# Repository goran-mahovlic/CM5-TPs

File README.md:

# CM5 Test Point Breakout

Sveden projekt za KiCad izveden iz obratno projektirane ploče Raspberry Pi Compute Module 5 ([schlae/cm5-reveng](https://github.com/schlae/cm5-reveng), CC BY-SA 4.0, autor Tube Time).

Sadrži **samo** ono što treba za pristup mjernim točkama modula:

| Element                        | Količina | Sloj         | Napomena                                                       |
|--------------------------------|----------|--------------|----------------------------------------------------------------|
| Test-točke `TP*`               | 58       | B.Cu (donji) | pad promjera 1,0 mm                                            |
| Konektori modula `J3`, `J4`    | 2        | B.Cu (donji) | Amphenol 10164228-1001A1RLF, 2 × 100 nožica + 4 mehanička pada |
| Rupe za pričvršćenje `H1`–`H4` | 4        | kroz ploču   | raspored 48,0 × 33,0 mm                                        |
| Obris ploče `Edge.Cuts`        | 8 crta   | –            | 55,00 × 40,00 mm, zaobljeni kutovi                             |

Vodovi, zone, ostale sastavnice i unutarnji slojevi izostavljeni su. Geometrija je preuzeta **1:1**, pa se položaji poklapaju s pravim modulom.

*Donji sloj: 58 test-točaka, konektori J3 (gore) i J4 (dolje), četiri rupe u uglovima. Natpisi J3/J4 zrcaljeni su jer su na donjem sloju.*

## Datoteke

```
cm5_tp_breakout.kicad_pro      projekt
cm5_tp_breakout.kicad_sch      korijenska shema (tri lista)
  testpoints.kicad_sch         58 test-točaka, opis uz svaku
  cm5_connectors.kicad_sch     J3 i J4 sa svim imenima mreža
  mechanical.kicad_sch         H1-H4
cm5_tp_breakout.kicad_pcb      ploča (dva sloja)
cm5_tp_breakout.kicad_sym      simboli (TestPoint, CM5_Conn_100P, MountingHole)
cm5_tp_breakout.pretty/        footprinti (izvezeni iz izvorne ploče)
doc/                           izvezena shema u PDF-u
tools/                         generator — projekt se može ponovno izgraditi iz izvornika
```

Projekt je samostalan: simboli i footprinti nalaze se u projektnim knjižnicama, pa ne treba nijedna vanjska knjižnica.

## Test-točke

Koordinate su u milimetrima od **donjega lijevog kuta ploče**, u KiCadovu pogledu odozgo (X udesno, Y prema gore). Točke su na donjem sloju, pa su pri pogledu odozdo zrcaljene po osi X.

`Oznaka` je natpis s izvorne ploče, `Mreža` je ime mreže u shemi, `Na konektoru` navodi nožice J3/J4 koje su na istoj mreži.

### Napajanje

| TP     | Oznaka       | Mreža            | Nazivno | X \[mm\] | Y \[mm\] | Na konektoru                             | Opis                                                                                                               |
|--------|--------------|------------------|---------|---------:|---------:|------------------------------------------|--------------------------------------------------------------------------------------------------------------------|
| `TP63` | 5V_SENSE     | `+5V`            | 5,0 V   |     8,70 |    18,20 | –                                        | 5 V iza sklopke s ograničenjem struje u PMIC-u DA9091; na ploči označeno 5V_SENSE — mjerna točka, ne opterećivati. |
| `TP1`  | 5V           | `+5VIN`          | 5,0 V   |    14,34 |    17,54 | J3-77, J3-79, J3-81, J3-83, J3-85, J3-87 | Ulazno napajanje modula s nosive ploče, prije sklopke PMIC-a (J3, nožice 77–87).                                   |
| `TP78` | 5V           | `+5VIN`          | 5,0 V   |    14,37 |    19,52 | J3-77, J3-79, J3-81, J3-83, J3-85, J3-87 | Ulazno napajanje modula s nosive ploče, prije sklopke PMIC-a (J3, nožice 77–87).                                   |
| `TP34` | CM5_1V8      | `CM5_1V8`        | 1,8 V   |    50,50 |    15,50 | J3-88, J3-90                             | Sabirnica 1,8 V modula izvedena na konektor (J3, nožice 88 i 90).                                                  |
| `TP33` | CM5_3V3      | `CM5_3V3`        | 3,3 V   |    47,00 |    36,00 | J3-84, J3-86                             | Sabirnica 3,3 V modula izvedena na konektor (J3, nožice 84 i 86).                                                  |
| `TP64` | VDD_1V0_PHY  | `ETHPHY_U4_VREG` | –       |    47,30 |     5,40 | –                                        | Izlaz unutarnjega regulatora ethernetskoga PHY-ja BCM54210PE (U4), nožica VREG; na ploči označeno VDD_1V0_PHY.     |
| `TP77` | GPIO_VREF    | `GPIO_VREF`      | 3,3 V   |    45,00 |    37,00 | J3-78                                    | Referentni napon skupine GPIO na RP1; određuje logičke razine (J3, nožica 78).                                     |
| `TP30` | 0V6          | `VDD_0V6`        | 0,6 V   |    37,20 |    34,90 | –                                        | VDDQ za LPDDR4X (U2) iz PMIC-a; osjetljivo na šum i pad napona.                                                    |
| `TP29` | VDD_0V8_BCM  | `VDD_0V8_BCM`    | 0,8 V   |    23,65 |    21,55 | –                                        | Pomoćna sabirnica 0,8 V za BCM2712.                                                                                |
| `TP15` | VDD_0V8_LDO  | `VDD_0V8_LDO`    | 0,8 V   |    14,70 |     6,60 | –                                        | Izlaz linearnoga regulatora 0,8 V (niskošumni dio).                                                                |
| `TP31` | 1V1          | `VDD_1V1`        | 1,1 V   |     9,10 |     3,20 | –                                        | Sabirnica 1,1 V (VDD1 memorije LPDDR4X i logika).                                                                  |
| `TP27` | VDD_1V1_RP1  | `VDD_1V1_RP1`    | 1,1 V   |    43,60 |    22,30 | –                                        | Jezgreno napajanje 1,1 V za ulazno-izlazni most RP1.                                                               |
| `TP45` | VDD_1V1_RP1  | `VDD_1V1_RP1`    | 1,1 V   |    53,10 |    28,70 | –                                        | Jezgreno napajanje 1,1 V za ulazno-izlazni most RP1.                                                               |
| `TP18` | VDD_1V8_2    | `VDD_1V8_2`      | 1,8 V   |    23,40 |    23,55 | –                                        | Druga grana 1,8 V (ulazi/izlazi i memorija).                                                                       |
| `TP44` | VDD_2V5_RP1  | `VDD_2V5_RP1`    | 2,5 V   |    51,70 |    30,20 | –                                        | Napajanje 2,5 V analognoga dijela RP1 (PLL i PHY).                                                                 |
| `TP17` | VDD_3V3_2    | `VDD_3V3_2`      | 3,3 V   |    37,40 |     8,10 | –                                        | Druga grana 3,3 V (ulazi/izlazi).                                                                                  |
| `TP32` | VDD_3V7_WIFI | `VDD_3V7_WIFI`   | 3,7 V   |     1,50 |    13,00 | –                                        | Napajanje modula WiFi/Bluetooth RP1-RM0 (U7).                                                                      |
| `TP28` | VDD_BCM_CORE | `VDD_BCM_CORE`   | ~0,8 V  |    15,40 |    16,00 | –                                        | Jezgreno napajanje SoC-a BCM2712; napon se mijenja s opterećenjem (DVFS).                                          |
| `TP9`  | VREF_3V3     | `VREF_3V3`       | 3,3 V   |     1,50 |    10,50 | –                                        | Referentnih 3,3 V (djelitelj napona, ne opterećivati).                                                             |
| `TP10` | VREG         | `VREG`           | –       |    48,40 |    15,10 | –                                        | Izlaz unutarnjega regulatora PMIC-a DA9091; mjerna točka, ne napajanje.                                            |

### Masa

| TP     | Oznaka | Mreža | Nazivno | X \[mm\] | Y \[mm\] | Na konektoru                         | Opis                                                           |
|--------|--------|-------|---------|---------:|---------:|--------------------------------------|----------------------------------------------------------------|
| `TP3`  | GND    | `GND` | 0 V     |    51,20 |    32,60 | J3-1, J3-2, J3-7, J3-8, J3-13, J3-14 | Masa. Referentna točka za sva mjerenja; devet točaka po ploči. |
| `TP7`  | GND    | `GND` | 0 V     |    24,20 |     7,50 | J3-1, J3-2, J3-7, J3-8, J3-13, J3-14 | Masa. Referentna točka za sva mjerenja; devet točaka po ploči. |
| `TP8`  | GND    | `GND` | 0 V     |     1,65 |    15,05 | J3-1, J3-2, J3-7, J3-8, J3-13, J3-14 | Masa. Referentna točka za sva mjerenja; devet točaka po ploči. |
| `TP13` | GND    | `GND` | 0 V     |    42,60 |     7,30 | J3-1, J3-2, J3-7, J3-8, J3-13, J3-14 | Masa. Referentna točka za sva mjerenja; devet točaka po ploči. |
| `TP26` | GND    | `GND` | 0 V     |    17,70 |    20,20 | J3-1, J3-2, J3-7, J3-8, J3-13, J3-14 | Masa. Referentna točka za sva mjerenja; devet točaka po ploči. |
| `TP46` | GND    | `GND` | 0 V     |     7,00 |    34,70 | J3-1, J3-2, J3-7, J3-8, J3-13, J3-14 | Masa. Referentna točka za sva mjerenja; devet točaka po ploči. |
| `TP60` | GND    | `GND` | 0 V     |    48,00 |    38,70 | J3-1, J3-2, J3-7, J3-8, J3-13, J3-14 | Masa. Referentna točka za sva mjerenja; devet točaka po ploči. |
| `TP61` | GND    | `GND` | 0 V     |     6,58 |     1,23 | J3-1, J3-2, J3-7, J3-8, J3-13, J3-14 | Masa. Referentna točka za sva mjerenja; devet točaka po ploči. |
| `TP62` | GND    | `GND` | 0 V     |    22,20 |    31,60 | J3-1, J3-2, J3-7, J3-8, J3-13, J3-14 | Masa. Referentna točka za sva mjerenja; devet točaka po ploči. |

### Upravljanje i pokretanje

| TP     | Oznaka     | Mreža          | Nazivno | X \[mm\] | Y \[mm\] | Na konektoru | Opis                                                                                                                 |
|--------|------------|----------------|---------|---------:|---------:|--------------|----------------------------------------------------------------------------------------------------------------------|
| `TP4`  | PMIC_INT   | `PMIC_INT`     | 3,3 V   |     4,80 |    13,00 | –            | Zahtjev za prekid iz PMIC-a DA9091 prema BCM2712 (djelatan niskom razinom).                                          |
| `TP39` | EN_LOAD_SW | `PWRSW_U10_ON` | –       |    22,10 |     6,10 | –            | Ulaz ON sklopke napajanja SLG59M1446V (U10); na ploči označeno EN_LOAD_SW, visoka razina znači uključenu sklopku.    |
| `TP42` | PWR_BUT    | `PWR_BUT`      | 3,3 V   |    11,40 |    34,90 | J3-92        | Tipka napajanja prema PMIC-u; kratki spoj na masu budi ili gasi modul.                                               |
| `TP2`  | RUN        | `RUN`          | 3,3 V   |     8,80 |     1,30 | –            | Opći ponovni postav (djelatan niskom razinom, s otporom prema napajanju). Kratki spoj na masu ponovno pokreće modul. |
| `TP21` | nRESET_OUT | `nRESET_OUT`   | 3,3 V   |    24,51 |    14,03 | –            | Izlazni ponovni postav prema sklopovlju nosive ploče; niska razina dok modul nije spreman.                           |
| `TP16` | nRPIBOOT   | `nRPIBOOT`     | 3,3 V   |     9,30 |    34,90 | J3-93        | Niska razina pri uključenju pokreće modul s USB-a (rpiboot) umjesto s eMMC-a.                                        |

### Otklanjanje pogrešaka (JTAG/UART)

| TP     | Oznaka        | Mreža           | Nazivno | X \[mm\] | Y \[mm\] | Na konektoru | Opis                                            |
|--------|---------------|-----------------|---------|---------:|---------:|--------------|-------------------------------------------------|
| `TP36` | DEBUG_UART_RX | `DEBUG_UART_RX` | 3,3 V   |     8,50 |    37,10 | –            | Serijska konzola, ulaz u modul.                 |
| `TP35` | DEBUG_UART_TX | `DEBUG_UART_TX` | 3,3 V   |    11,00 |    37,80 | –            | Serijska konzola, izlaz iz modula (115200 8N1). |
| `TP52` | SOC_TCK       | `SOC_TCK`       | 3,3 V   |    19,90 |    11,90 | –            | Takt JTAG prema BCM2712.                        |
| `TP49` | SOC_TDI       | `SOC_TDI`       | 3,3 V   |    21,60 |    13,30 | –            | Ulaz podataka JTAG.                             |
| `TP50` | SOC_TDO       | `SOC_TDO`       | 3,3 V   |    20,40 |    17,20 | –            | Izlaz podataka JTAG.                            |
| `TP51` | SOC_TMS       | `SOC_TMS`       | 3,3 V   |    20,30 |     8,80 | –            | Odabir načina rada JTAG.                        |
| `TP48` | SOC_TRST_N    | `SOC_TRST_N`    | 3,3 V   |    21,60 |    15,40 | –            | Ponovni postav JTAG (djelatan niskom razinom).  |

### Sabirnica I2C prema PMIC-u

| TP     | Oznaka   | Mreža          | Nazivno | X \[mm\] | Y \[mm\] | Na konektoru | Opis                                                              |
|--------|----------|----------------|---------|---------:|---------:|--------------|-------------------------------------------------------------------|
| `TP40` | PMIC_SCL | `PMIC_I2C.SCL` | 3,3 V   |     6,70 |    15,20 | –            | Takt sabirnice I2C prema PMIC-u DA9091 — put do registara PMIC-a. |
| `TP41` | PMIC_SDA | `PMIC_I2C.SDA` | 3,3 V   |     8,70 |    15,30 | –            | Podatci sabirnice I2C prema PMIC-u DA9091.                        |

### Ethernet 1000BASE-T

| TP     | Oznaka | Mreža     | Nazivno | X \[mm\] | Y \[mm\] | Na konektoru | Opis                                                                     |
|--------|--------|-----------|---------|---------:|---------:|--------------|--------------------------------------------------------------------------|
| `TP70` | ETH0_N | `ETH.0_N` | par     |    39,60 |    24,20 | J3-10        | Ethernetski par A, negativni vod.                                        |
| `TP69` | ETH0_P | `ETH.0_P` | par     |    38,80 |    25,90 | J3-12        | Ethernetski par A, pozitivni vod (od PHY-ja BCM54210PE prema konektoru). |
| `TP71` | ETH1_N | `ETH.1_N` | par     |    43,80 |    14,10 | J3-6         | Ethernetski par B, negativni vod.                                        |
| `TP72` | ETH1_P | `ETH.1_P` | par     |    45,60 |    13,10 | J3-4         | Ethernetski par B, pozitivni vod.                                        |
| `TP74` | ETH2_N | `ETH.2_N` | par     |    42,60 |    33,70 | J3-9         | Ethernetski par C, negativni vod.                                        |
| `TP73` | ETH2_P | `ETH.2_P` | par     |    42,40 |    31,70 | J3-11        | Ethernetski par C, pozitivni vod.                                        |
| `TP76` | ETH3_N | `ETH.3_N` | par     |    42,90 |    36,10 | J3-5         | Ethernetski par D, negativni vod.                                        |
| `TP75` | ETH3_P | `ETH.3_P` | par     |    41,60 |    37,80 | J3-3         | Ethernetski par D, pozitivni vod.                                        |

### USB 2.0

| TP     | Oznaka   | Mreža     | Nazivno | X \[mm\] | Y \[mm\] | Na konektoru | Opis                                                             |
|--------|----------|-----------|---------|---------:|---------:|--------------|------------------------------------------------------------------|
| `TP65` | USBC_D_N | `USBC.DM` | par     |    28,20 |     7,50 | J4-3         | USB 2.0 D− prema konektoru (J4, nožica 3); rabi se i za rpiboot. |
| `TP66` | USBC_D_P | `USBC.DP` | par     |    26,10 |     7,50 | J4-5         | USB 2.0 D+ prema konektoru (J4, nožica 5).                       |

### Signalne svjetiljke

| TP     | Oznaka   | Mreža      | Nazivno | X \[mm\] | Y \[mm\] | Na konektoru | Opis                                                                         |
|--------|----------|------------|---------|---------:|---------:|--------------|------------------------------------------------------------------------------|
| `TP68` | LED_nACT | `LED_nACT` | 3,3 V   |    13,00 |    37,50 | J3-21        | Upravljanje svjetiljkom aktivnosti (djelatno niskom razinom, J3, nožica 21). |
| `TP67` | LED_nPWR | `LED_nPWR` | 3,3 V   |     7,00 |    38,60 | J3-95        | Upravljanje svjetiljkom napajanja (djelatno niskom razinom, J3, nožica 95).  |

### Ostalo

| TP     | Oznaka   | Mreža           | Nazivno | X \[mm\] | Y \[mm\] | Na konektoru | Opis                                                                                                                |
|--------|----------|-----------------|---------|---------:|---------:|--------------|---------------------------------------------------------------------------------------------------------------------|
| `TP22` | PMIC_SIG | `PMIC_U5_PIN48` | –       |    13,09 |    11,23 | –            | Točka na nožici 48 PMIC-a DA9091 (U5), na ploči označena PMIC_SIG; u izvornoj shemi mreža nema ime.                 |
| `TP57` | RP1_TP   | `RPU4`          | –       |    53,20 |    32,00 | –            | Veza RP1 (U3, kuglica E12) i BCM2712 (U1, kuglica AD1), na ploči označena RP1_TP; izvorna shema ne opisuje namjenu. |

## Mjerne napomene

- **Masa** ima devet točaka; za brze signale uzmi onu najbližu mjernoj točki i kratku petlju sonde.
- **Ethernet i USB** diferencijalni su parovi. Test-točka je odvojak s voda: sonda unosi kapacitet i kvari prilagodbu, pa mjeri samo kad je nužno i s najmanjom mogućom sondom.
- **RUN** i **PWR_BUT** kratkim spojem na masu izazivaju ponovno pokretanje, odnosno buđenje. Ne drži ih trajno na masi.
- **nRPIBOOT** mora biti na niskoj razini *u trenutku uključenja* da bi modul ušao u način rada rpiboot.
- **PMIC_I2C** radna je sabirnica prema PMIC-u; upis u registre može ugasiti napajanje modula.
- Jezgrena napajanja (`VDD_BCM_CORE`, `VDD_0V8*`) mijenjaju napon s opterećenjem — vrijednost u tablici okvirna je, nije granica ispravnosti.

## Provjere

Stanje pri zadnjem generiranju (`kicad-cli` 9.0.2):

| Provjera                                        | Rezultat                                                                                          |
|-------------------------------------------------|---------------------------------------------------------------------------------------------------|
| ERC (shema): pogreške                           | **0**                                                                                             |
| ERC (shema): upozorenja                         | 152 × `global_label_dangling` — oznaka mreže koja postoji samo na jednome mjestu                  |
| Popis mreža: shema prema ploči                  | 172 mreže i 260 čvorova, **istovjetno**                                                           |
| DRC: podudarnost sa shemom (`schematic_parity`) | **0 razlika**                                                                                     |
| DRC: nespojeni elementi                         | 94 — očekivano, ploča namjerno nema vodove                                                        |
| DRC: pogreške                                   | 6 × preklapanje dvorišta (TP1–TP78, TP1–TP28, TP2–TP31, TP7–TP66, TP69–TP70, TP68–J3)             |
| DRC: upozorenja                                 | 229 — natpis preko bakra (62), debljina teksta (58), visina teksta (58), preklapanje natpisa (51) |

Sve pogreške i upozorenja naslijeđeni su iz izvorne ploče: test-točke ondje su gusto postavljene, a natpisi sitni. Geometrija je namjerno preuzeta neizmijenjena, pa se položaji poklapaju s pravim modulom — pomicanje točaka radi čiste provjere DRC uništilo bi jedinu svrhu ovoga projekta.

Upozorenja o oznakama znače da ta mreža u ovome projektu postoji samo na jednome mjestu (npr. nožica GPIO na J3 bez pripadne test-točke). To je očekivano jer je ostatak modula izostavljen.

Nespojene veze pokazuju koje test-točke dijele mrežu s nožicom konektora — to je ovdje korisna obavijest, a ne pogreška.

## Ponovno generiranje

```bash
git clone --depth 1 https://github.com/schlae/cm5-reveng.git ~/.tmp/cm5-reveng
cd tools && python3 gen_all.py
```

Generator je determiniran (UUID-ovi se računaju iz imena), pa ponovno pokretanje daje datoteke bez lažne razlike u gitu.

## Licencija i podrijetlo

Geometrija, imena mreža i footprinti potječu iz projekta [schlae/cm5-reveng](https://github.com/schlae/cm5-reveng) (CC BY-SA 4.0). Ovaj izvedeni projekt nasljeđuje istu licenciju.

Izvorni autor izrijekom napominje da ploča **nije za proizvodnju**: parametri cjelovitosti signala nisu točni, footprinti se ne poklapaju savršeno, a popis materijala nije rekonstruiran. Isto vrijedi i ovdje — projekt služi za snalaženje i mjerenje, ne za izradu.

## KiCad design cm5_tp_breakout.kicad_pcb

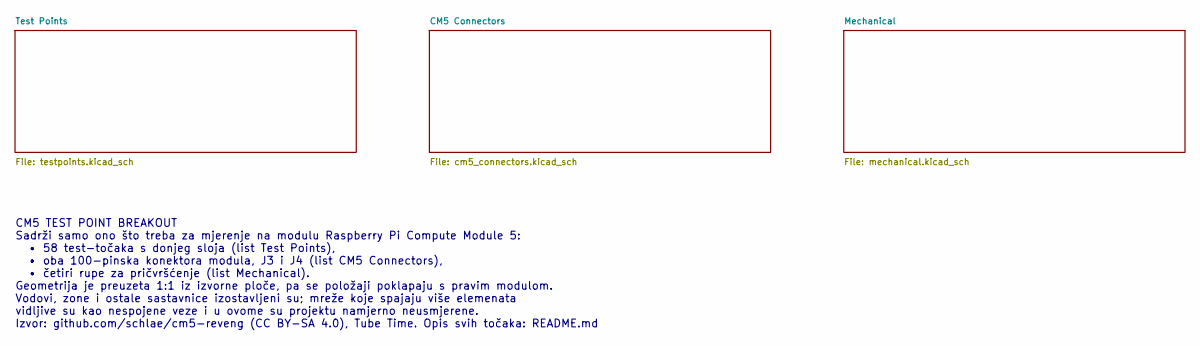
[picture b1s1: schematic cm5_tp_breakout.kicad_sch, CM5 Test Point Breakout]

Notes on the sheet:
CM5 TEST POINT BREAKOUT Sadrži samo ono što treba za mjerenje na modulu Raspberry Pi Compute Module 5: • 58 test-točaka s donjeg sloja (list Test Points), • oba 100-pinska konektora modula, J3 i J4 (list CM5 Connectors), • četiri rupe za pričvršćenje (list Mechanical). Geometrija je preuzeta 1:1 iz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

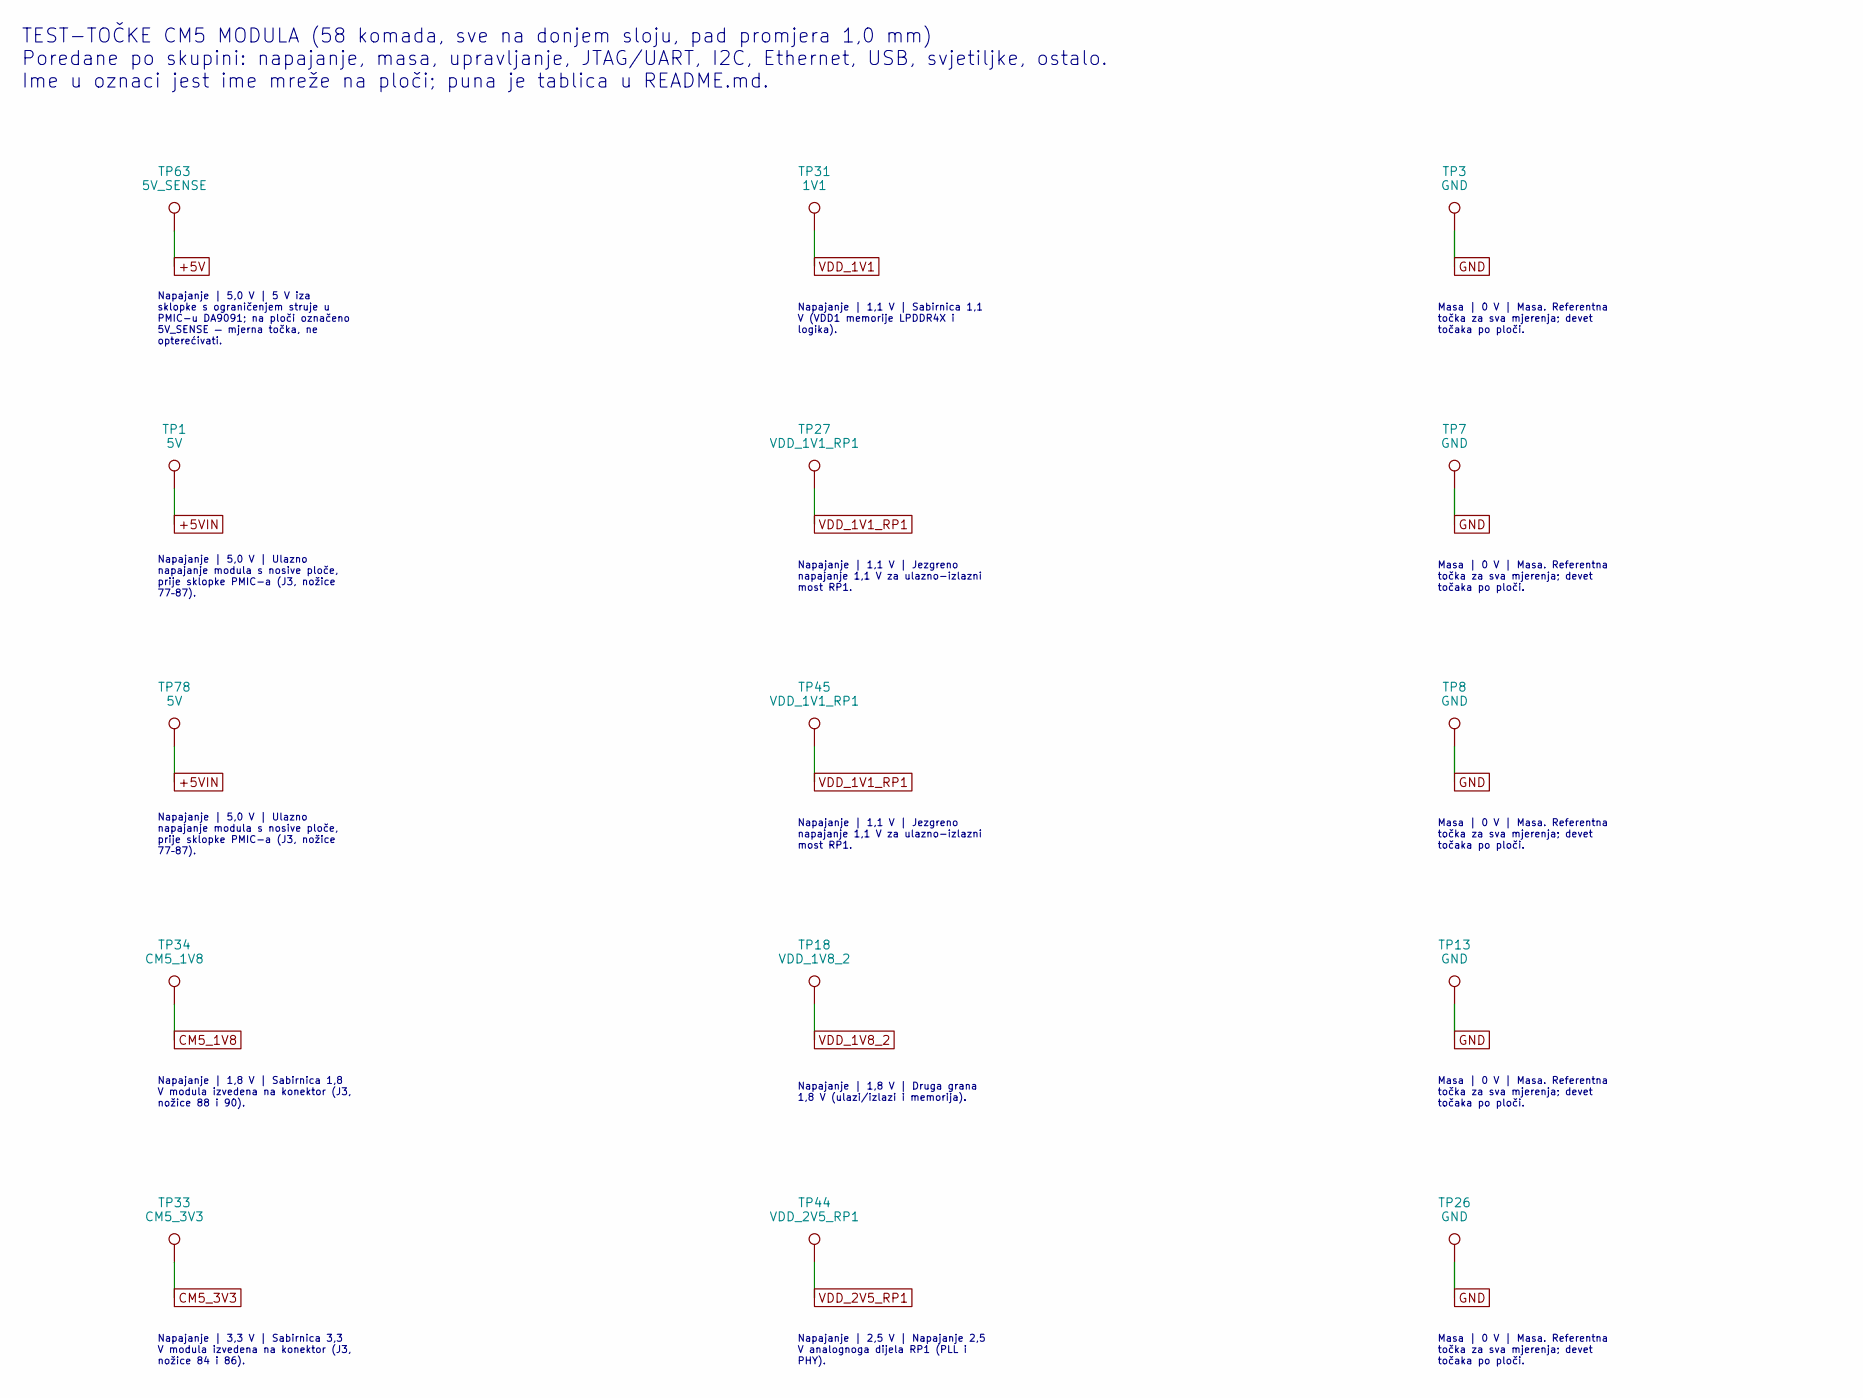
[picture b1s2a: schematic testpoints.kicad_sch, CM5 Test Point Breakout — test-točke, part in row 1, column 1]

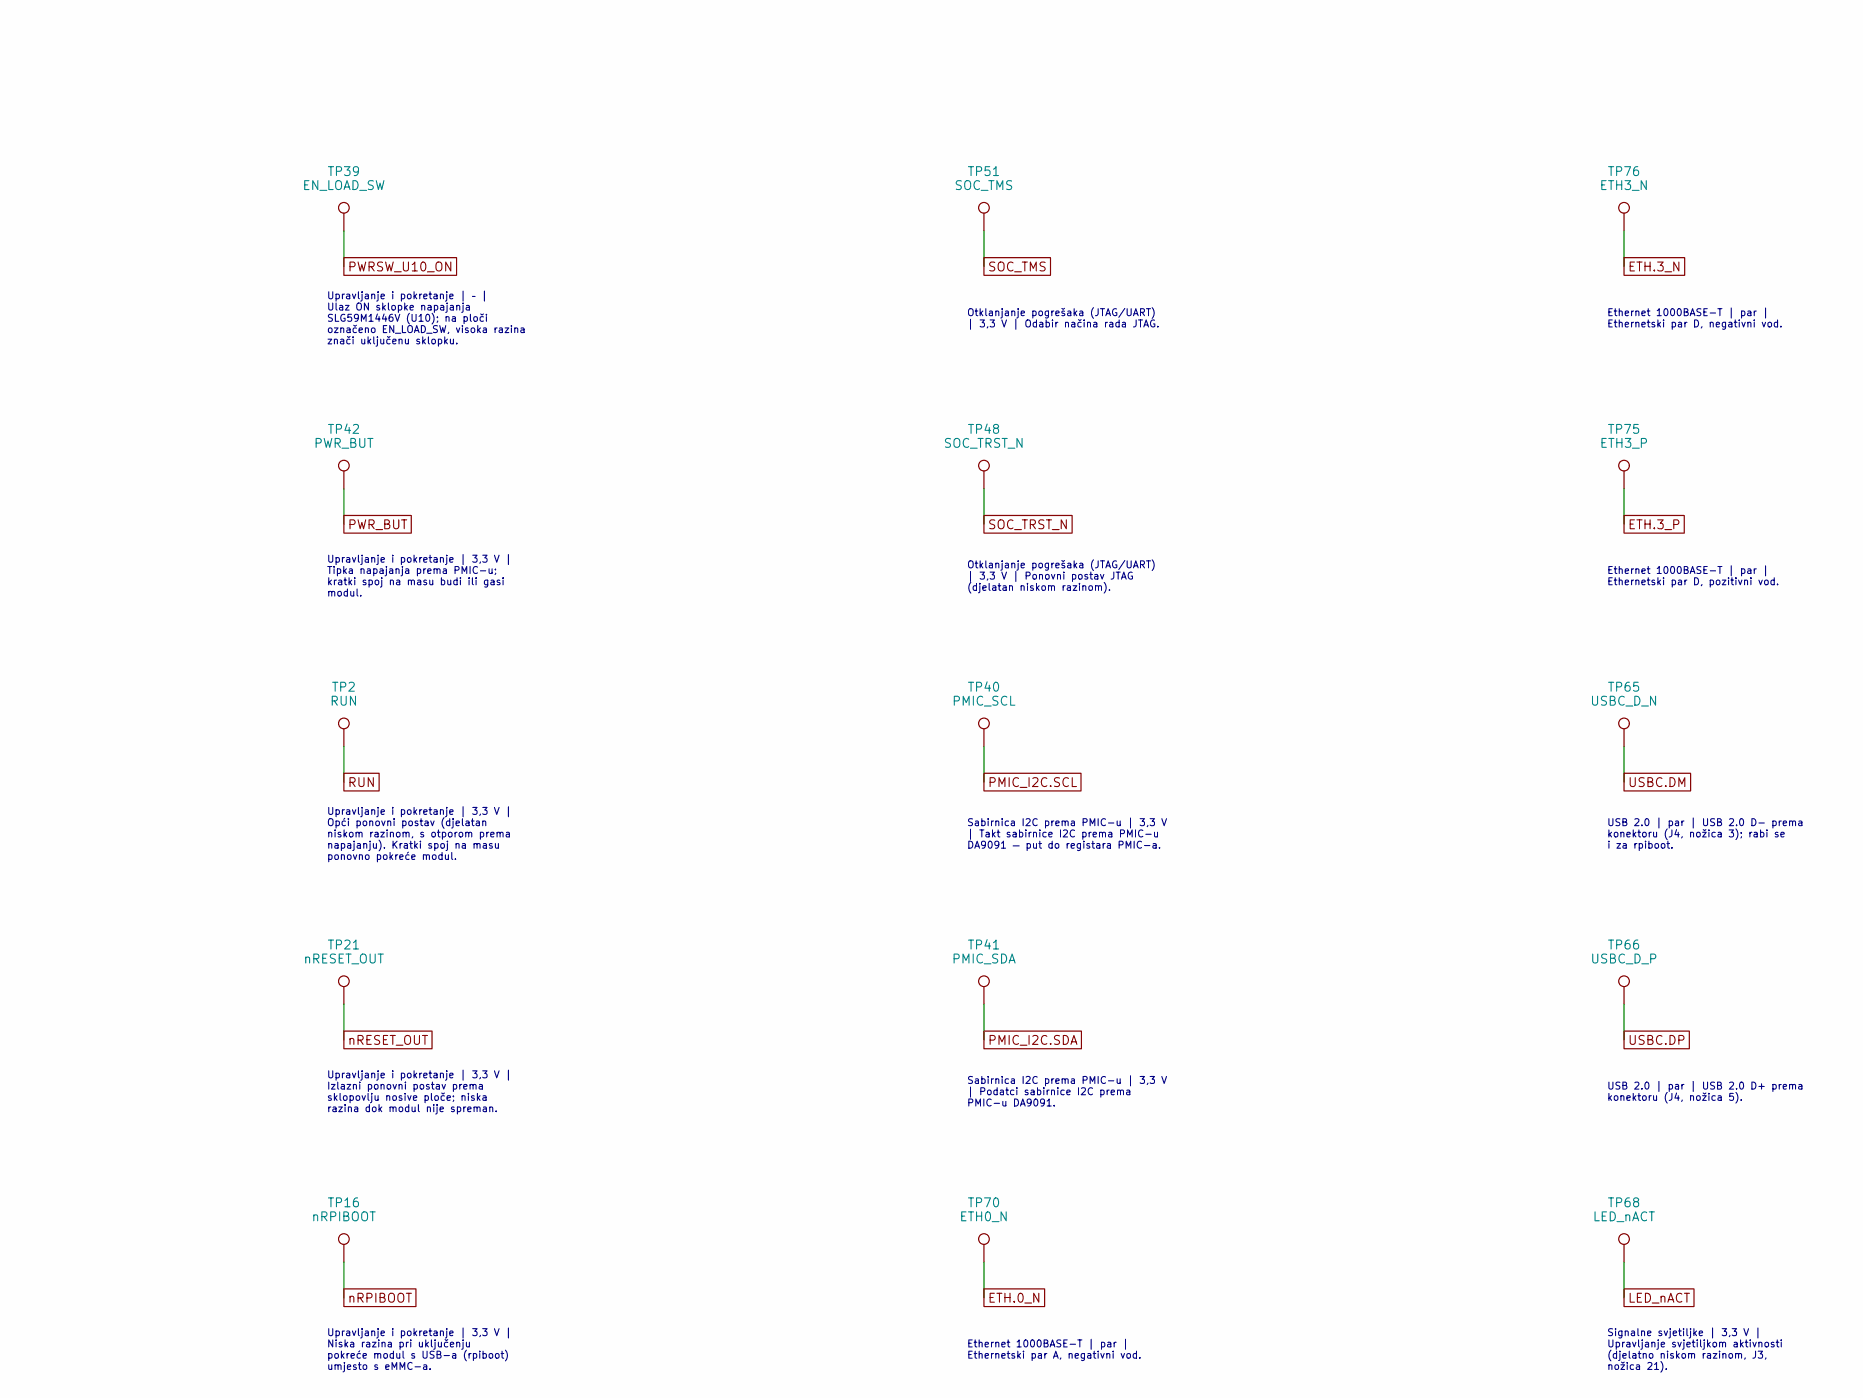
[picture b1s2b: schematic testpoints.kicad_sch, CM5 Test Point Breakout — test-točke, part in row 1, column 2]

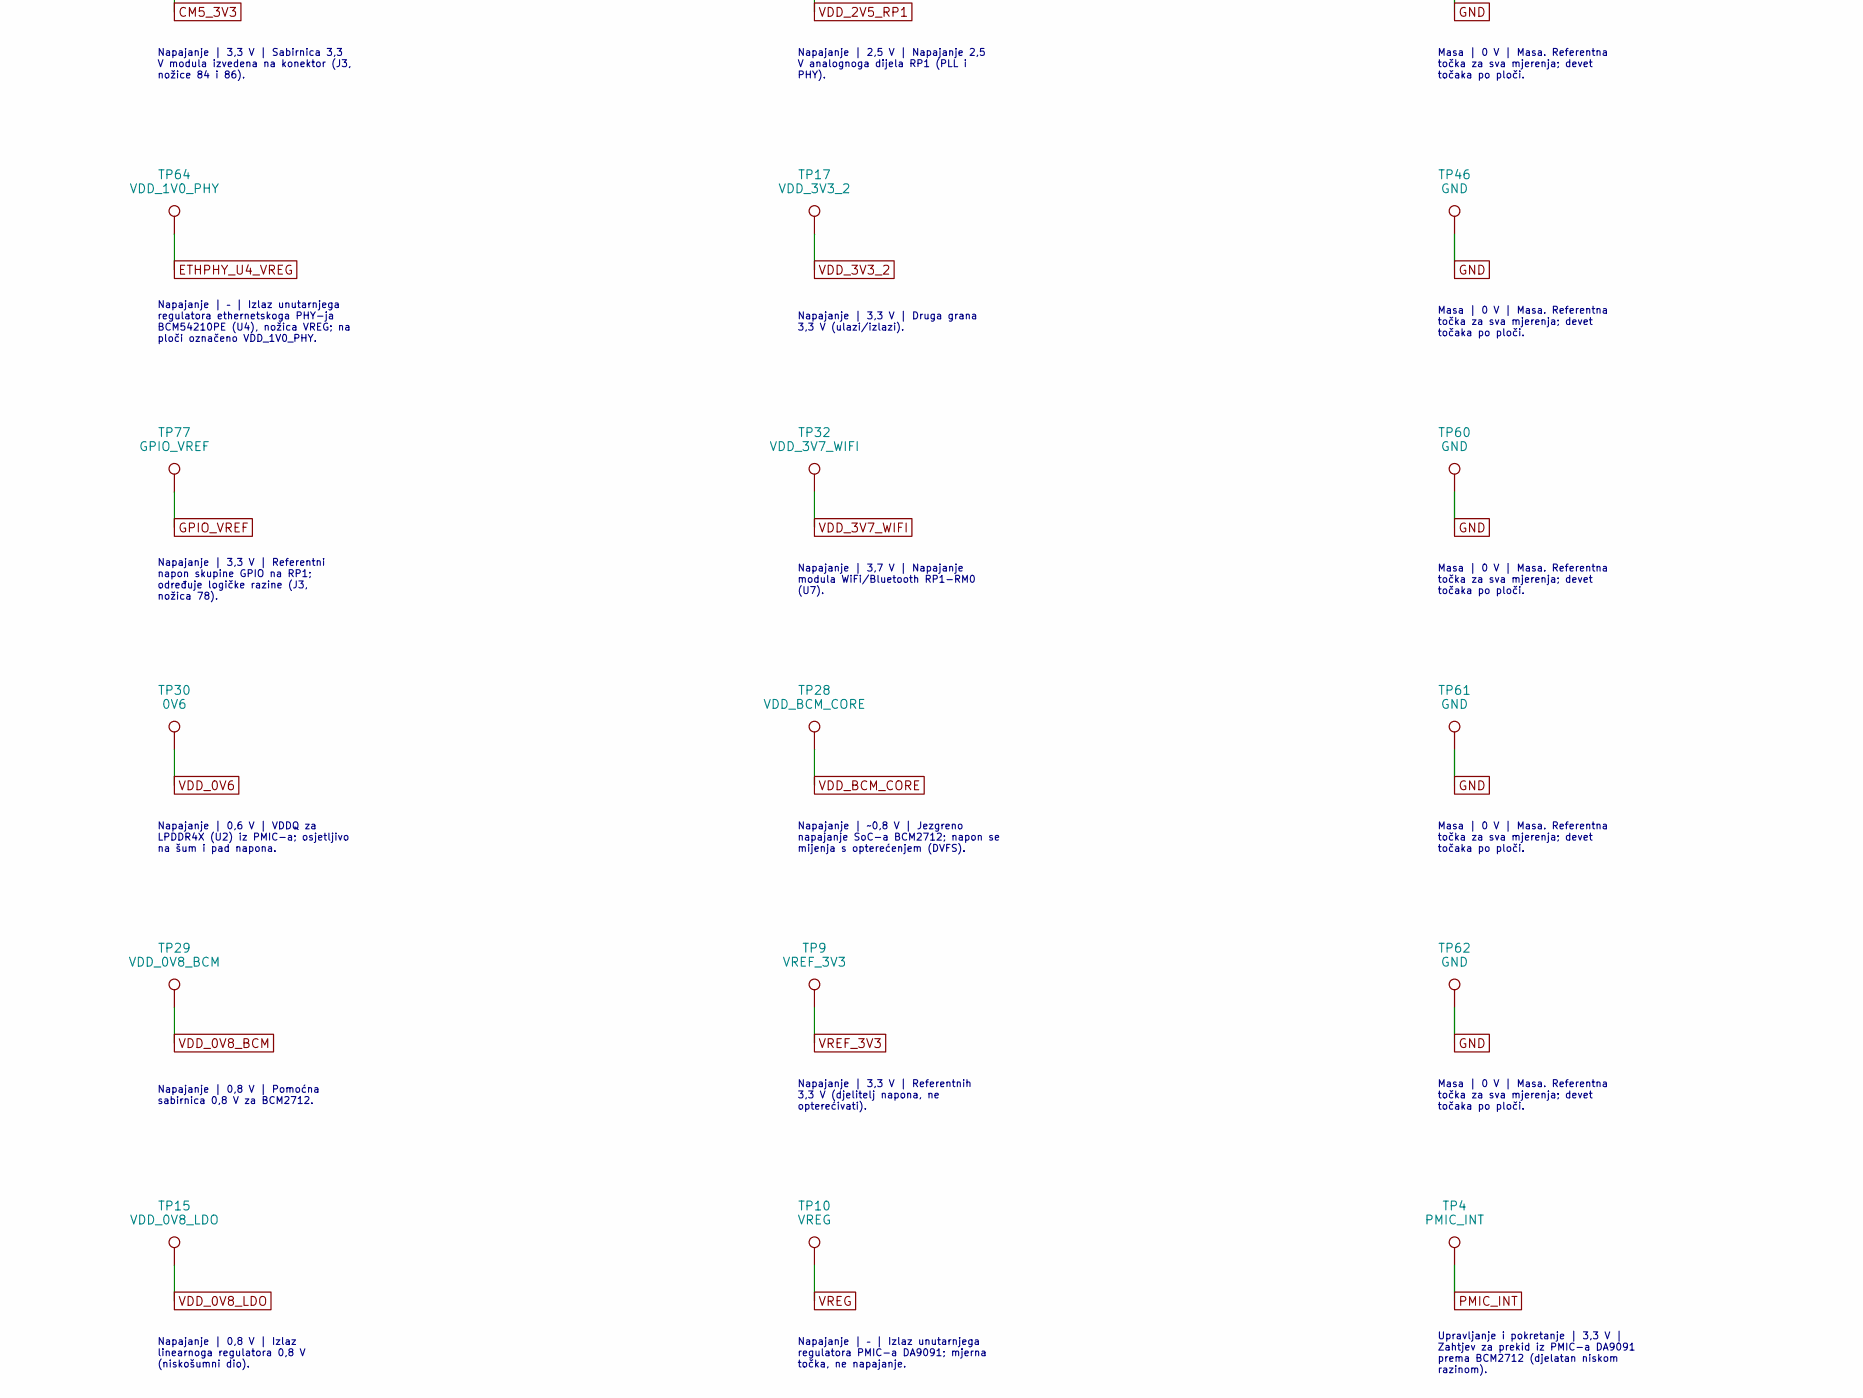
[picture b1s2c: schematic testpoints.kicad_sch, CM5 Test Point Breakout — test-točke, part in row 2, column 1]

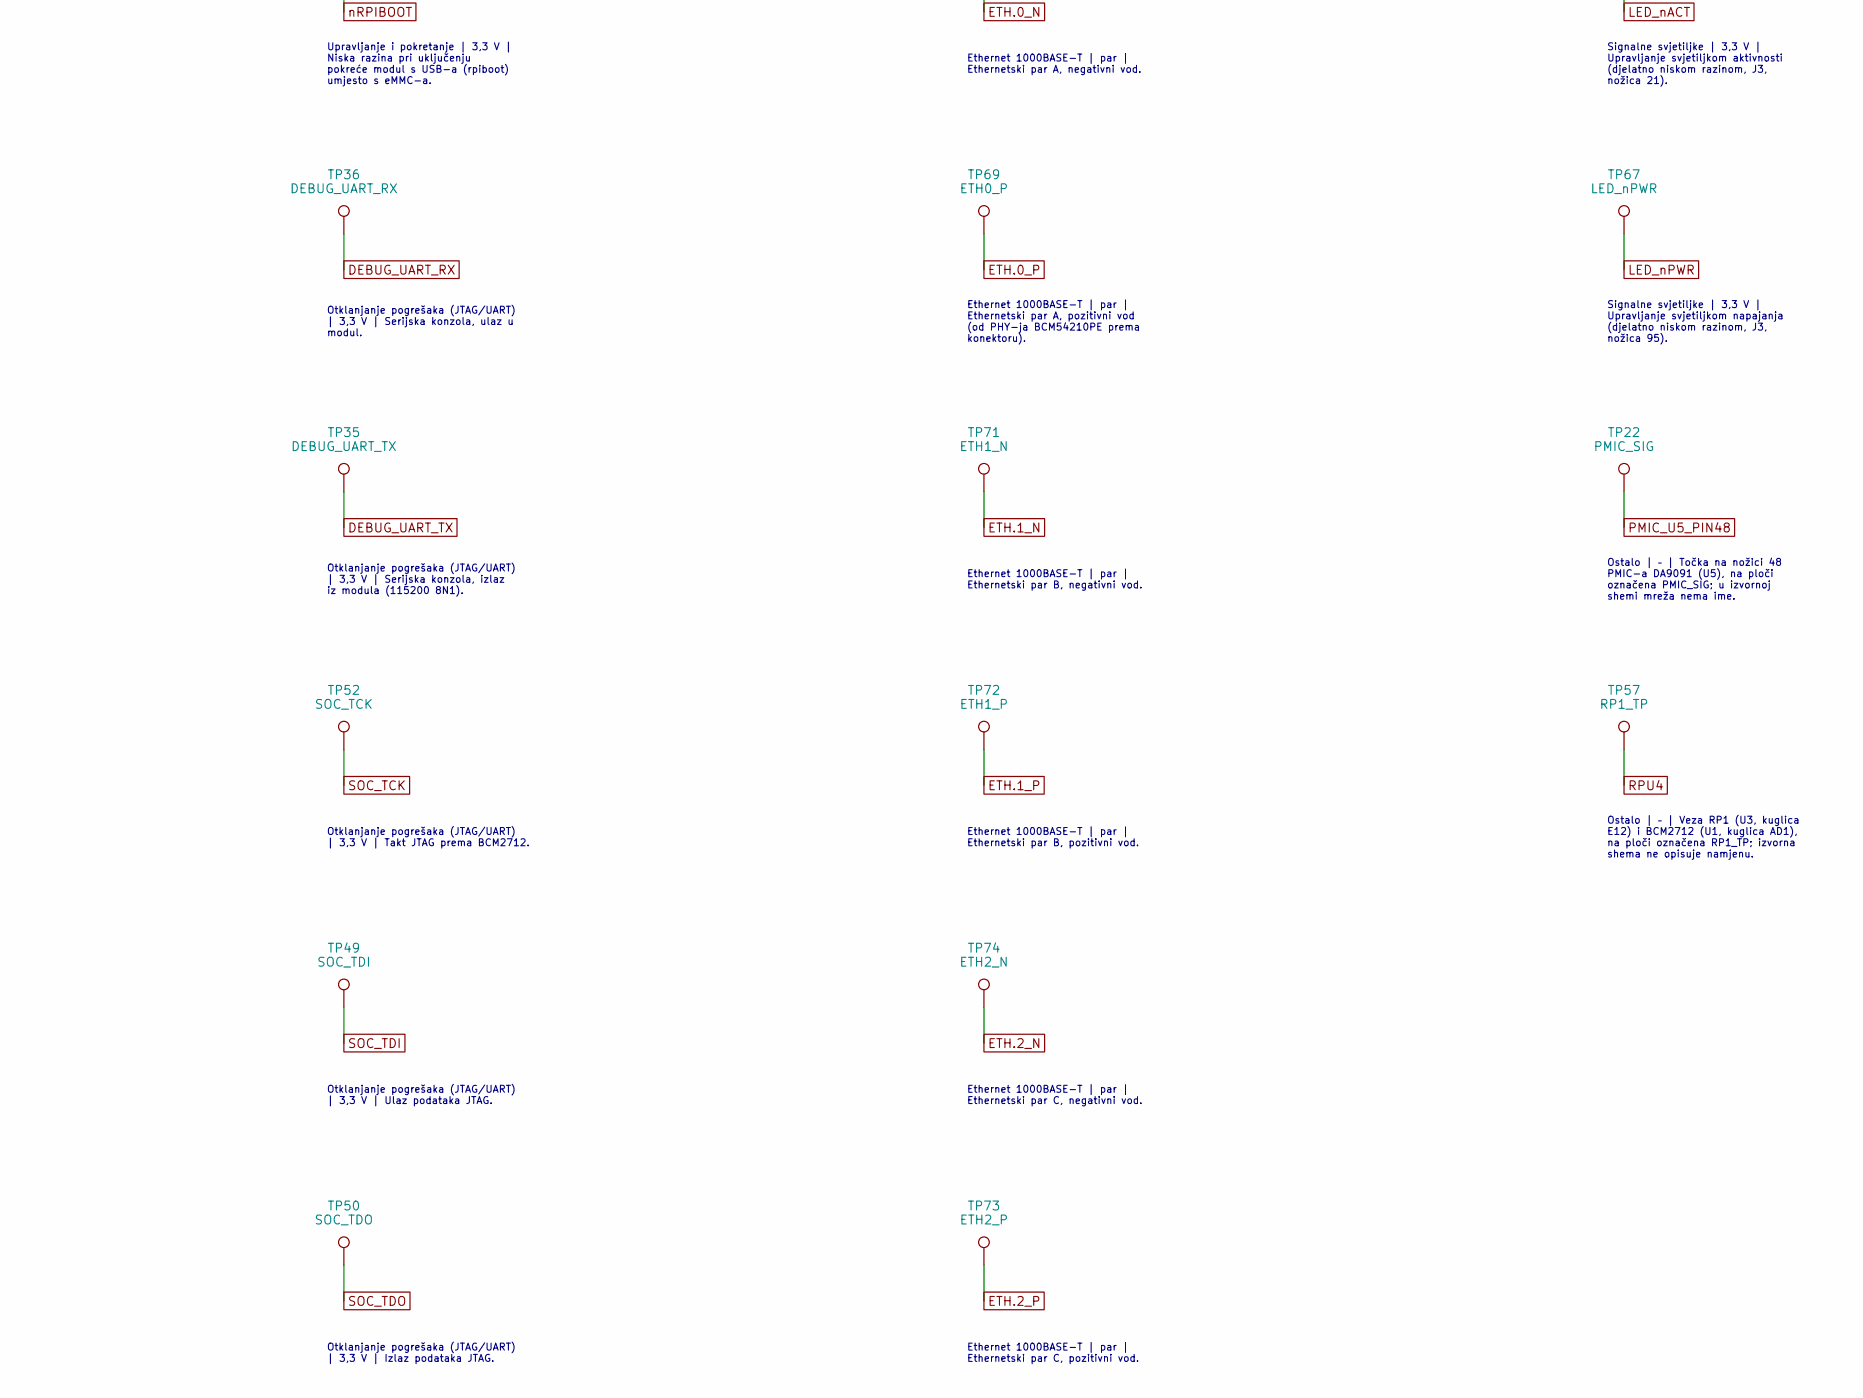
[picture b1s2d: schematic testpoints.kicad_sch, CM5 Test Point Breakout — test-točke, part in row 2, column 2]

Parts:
TP1, TP78: 5V; TestPoint_Pad_D1.0mm
TP2: RUN; TestPoint_Pad_D1.0mm
TP3, TP7, TP8, TP13, TP26, TP46, TP60, TP61, TP62: GND; TestPoint_Pad_D1.0mm
TP4: PMIC_INT; TestPoint_Pad_D1.0mm
TP9: VREF_3V3; TestPoint_Pad_D1.0mm
TP10: VREG; TestPoint_Pad_D1.0mm
TP15: VDD_0V8_LDO; TestPoint_Pad_D1.0mm
TP16: nRPIBOOT; TestPoint_Pad_D1.0mm
TP17: VDD_3V3_2; TestPoint_Pad_D1.0mm
TP18: VDD_1V8_2; TestPoint_Pad_D1.0mm
TP21: nRESET_OUT; TestPoint_Pad_D1.0mm
TP22: PMIC_SIG; TestPoint_Pad_D1.0mm
TP27, TP45: VDD_1V1_RP1; TestPoint_Pad_D1.0mm
TP28: VDD_BCM_CORE; TestPoint_Pad_D1.0mm
TP29: VDD_0V8_BCM; TestPoint_Pad_D1.0mm
TP30: 0V6; TestPoint_Pad_D1.0mm
TP31: 1V1; TestPoint_Pad_D1.0mm
TP32: VDD_3V7_WIFI; TestPoint_Pad_D1.0mm
TP33: CM5_3V3; TestPoint_Pad_D1.0mm
TP34: CM5_1V8; TestPoint_Pad_D1.0mm
TP35: DEBUG_UART_TX; TestPoint_Pad_D1.0mm
TP36: DEBUG_UART_RX; TestPoint_Pad_D1.0mm
TP39: EN_LOAD_SW; TestPoint_Pad_D1.0mm
TP40: PMIC_SCL; TestPoint_Pad_D1.0mm
TP41: PMIC_SDA; TestPoint_Pad_D1.0mm
TP42: PWR_BUT; TestPoint_Pad_D1.0mm
TP44: VDD_2V5_RP1; TestPoint_Pad_D1.0mm
TP48: SOC_TRST_N; TestPoint_Pad_D1.0mm
TP49: SOC_TDI; TestPoint_Pad_D1.0mm
TP50: SOC_TDO; TestPoint_Pad_D1.0mm
TP51: SOC_TMS; TestPoint_Pad_D1.0mm
TP52: SOC_TCK; TestPoint_Pad_D1.0mm
TP57: RP1_TP; TestPoint_Pad_D1.0mm
TP63: 5V_SENSE; TestPoint_Pad_D1.0mm
TP64: VDD_1V0_PHY; TestPoint_Pad_D1.0mm
TP65: USBC_D_N; TestPoint_Pad_D1.0mm
TP66: USBC_D_P; TestPoint_Pad_D1.0mm
TP67: LED_nPWR; TestPoint_Pad_D1.0mm
TP68: LED_nACT; TestPoint_Pad_D1.0mm
TP69: ETH0_P; TestPoint_Pad_D1.0mm
TP70: ETH0_N; TestPoint_Pad_D1.0mm
TP71: ETH1_N; TestPoint_Pad_D1.0mm
TP72: ETH1_P; TestPoint_Pad_D1.0mm
TP73: ETH2_P; TestPoint_Pad_D1.0mm
TP74: ETH2_N; TestPoint_Pad_D1.0mm
TP75: ETH3_P; TestPoint_Pad_D1.0mm
TP76: ETH3_N; TestPoint_Pad_D1.0mm
TP77: GPIO_VREF; TestPoint_Pad_D1.0mm

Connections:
+5V: TP63.1
+5VIN: TP1.1, TP78.1; also elsewhere on the board
CM5_1V8: TP34.1; also elsewhere on the board
CM5_3V3: TP33.1; also elsewhere on the board
DEBUG_UART_RX: TP36.1
DEBUG_UART_TX: TP35.1
ETH.0_N: TP70.1; also elsewhere on the board
ETH.0_P: TP69.1; also elsewhere on the board
ETH.1_N: TP71.1; also elsewhere on the board
ETH.1_P: TP72.1; also elsewhere on the board
ETH.2_N: TP74.1; also elsewhere on the board
ETH.2_P: TP73.1; also elsewhere on the board
ETH.3_N: TP76.1; also elsewhere on the board
ETH.3_P: TP75.1; also elsewhere on the board
ETHPHY_U4_VREG: TP64.1
GND: TP3.1, TP7.1, TP8.1, TP13.1, TP26.1, TP46.1, TP60.1, TP61.1, TP62.1; also elsewhere on the board
GPIO_VREF: TP77.1; also elsewhere on the board
LED_nACT: TP68.1; also elsewhere on the board
LED_nPWR: TP67.1; also elsewhere on the board
PMIC_I2C.SCL: TP40.1
PMIC_I2C.SDA: TP41.1
PMIC_INT: TP4.1
PMIC_U5_PIN48: TP22.1
PWRSW_U10_ON: TP39.1
PWR_BUT: TP42.1; also elsewhere on the board
RPU4: TP57.1
RUN: TP2.1
SOC_TCK: TP52.1
SOC_TDI: TP49.1
SOC_TDO: TP50.1
SOC_TMS: TP51.1
SOC_TRST_N: TP48.1
USBC.DM: TP65.1; also elsewhere on the board
USBC.DP: TP66.1; also elsewhere on the board
VDD_0V6: TP30.1
VDD_0V8_BCM: TP29.1
VDD_0V8_LDO: TP15.1
VDD_1V1: TP31.1
VDD_1V1_RP1: TP27.1, TP45.1
VDD_1V8_2: TP18.1
VDD_2V5_RP1: TP44.1
VDD_3V3_2: TP17.1
VDD_3V7_WIFI: TP32.1
VDD_BCM_CORE: TP28.1
VREF_3V3: TP9.1
VREG: TP10.1
nRESET_OUT: TP21.1
nRPIBOOT: TP16.1; also elsewhere on the board

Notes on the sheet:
TEST-TOČKE CM5 MODULA (58 komada, sve na donjem sloju, pad promjera 1,0 mm) Poredane po skupini: napajanje, masa, upravljanje, JTAG/UART, I2C, Ethernet, USB, svjetiljke, ostalo. Ime u oznaci jest ime mreže na ploči; puna je tablica u README.md.
Napajanje | 5,0 V | 5 V iza sklopke s ograničenjem struje u PMIC-u DA9091; na ploči označeno 5V_SENSE — mjerna točka, ne opterećivati.
Napajanje | 5,0 V | Ulazno napajanje modula s nosive ploče, prije sklopke PMIC-a (J3, nožice 77–87).
Napajanje | 1,8 V | Sabirnica 1,8 V modula izvedena na konektor (J3, nožice 88 i 90).
Napajanje | 3,3 V | Sabirnica 3,3 V modula izvedena na konektor (J3, nožice 84 i 86).
Napajanje | – | Izlaz unutarnjega regulatora ethernetskoga PHY-ja BCM54210PE (U4), nožica VREG; na ploči označeno VDD_1V0_PHY.
Napajanje | 3,3 V | Referentni napon skupine GPIO na RP1; određuje logičke razine (J3, nožica 78).
Napajanje | 0,6 V | VDDQ za LPDDR4X (U2) iz PMIC-a; osjetljivo na šum i pad napona.
Napajanje | 0,8 V | Pomoćna sabirnica 0,8 V za BCM2712.
Napajanje | 0,8 V | Izlaz linearnoga regulatora 0,8 V (niskošumni dio).
Napajanje | 1,1 V | Sabirnica 1,1 V (VDD1 memorije LPDDR4X i logika).
Napajanje | 1,1 V | Jezgreno napajanje 1,1 V za ulazno-izlazni most RP1.
Napajanje | 1,8 V | Druga grana 1,8 V (ulazi/izlazi i memorija).
Napajanje | 2,5 V | Napajanje 2,5 V analognoga dijela RP1 (PLL i PHY).
Napajanje | 3,3 V | Druga grana 3,3 V (ulazi/izlazi).
Napajanje | 3,7 V | Napajanje modula WiFi/Bluetooth RP1-RM0 (U7).
Napajanje | ~0,8 V | Jezgreno napajanje SoC-a BCM2712; napon se mijenja s opterećenjem (DVFS).
Napajanje | 3,3 V | Referentnih 3,3 V (djelitelj napona, ne opterećivati).
Napajanje | – | Izlaz unutarnjega regulatora PMIC-a DA9091; mjerna točka, ne napajanje.
Masa | 0 V | Masa. Referentna točka za sva mjerenja; devet točaka po ploči.
Upravljanje i pokretanje | 3,3 V | Zahtjev za prekid iz PMIC-a DA9091 prema BCM2712 (djelatan niskom razinom).
Upravljanje i pokretanje | – | Ulaz ON sklopke napajanja SLG59M1446V (U10); na ploči označeno EN_LOAD_SW, visoka razina znači uključenu sklopku.
Upravljanje i pokretanje | 3,3 V | Tipka napajanja prema PMIC-u; kratki spoj na masu budi ili gasi modul.
Upravljanje i pokretanje | 3,3 V | Opći ponovni postav (djelatan niskom razinom, s otporom prema napajanju). Kratki spoj na masu ponovno pokreće modul.
Upravljanje i pokretanje | 3,3 V | Izlazni ponovni postav prema sklopovlju nosive ploče; niska razina dok modul nije spreman.
Upravljanje i pokretanje | 3,3 V | Niska razina pri uključenju pokreće modul s USB-a (rpiboot) umjesto s eMMC-a.
Otklanjanje pogrešaka (JTAG/UART) | 3,3 V | Serijska konzola, ulaz u modul.
Otklanjanje pogrešaka (JTAG/UART) | 3,3 V | Serijska konzola, izlaz iz modula (115200 8N1).
Otklanjanje pogrešaka (JTAG/UART) | 3,3 V | Takt JTAG prema BCM2712.
Otklanjanje pogrešaka (JTAG/UART) | 3,3 V | Ulaz podataka JTAG.
Otklanjanje pogrešaka (JTAG/UART) | 3,3 V | Izlaz podataka JTAG.
Otklanjanje pogrešaka (JTAG/UART) | 3,3 V | Odabir načina rada JTAG.
Otklanjanje pogrešaka (JTAG/UART) | 3,3 V | Ponovni postav JTAG (djelatan niskom razinom).
Sabirnica I2C prema PMIC-u | 3,3 V | Takt sabirnice I2C prema PMIC-u DA9091 — put do registara PMIC-a.
Sabirnica I2C prema PMIC-u | 3,3 V | Podatci sabirnice I2C prema PMIC-u DA9091.
Ethernet 1000BASE-T | par | Ethernetski par A, negativni vod.
Ethernet 1000BASE-T | par | Ethernetski par A, pozitivni vod (od PHY-ja BCM54210PE prema konektoru).
Ethernet 1000BASE-T | par | Ethernetski par B, negativni vod.
Ethernet 1000BASE-T | par | Ethernetski par B, pozitivni vod.
Ethernet 1000BASE-T | par | Ethernetski par C, negativni vod.

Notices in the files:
cm5_connectors.kicad_sch:
izvedeno iz schlae/cm5-reveng, CC BY-SA 4.0
cm5_tp_breakout.kicad_sch:
Izvor: github.com/schlae/cm5-reveng (CC BY-SA 4.0), Tube Time. Opis svih točaka: README.md
